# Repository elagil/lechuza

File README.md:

# Lechuza (owl)

A columnar-stagger single-piece keyboard.

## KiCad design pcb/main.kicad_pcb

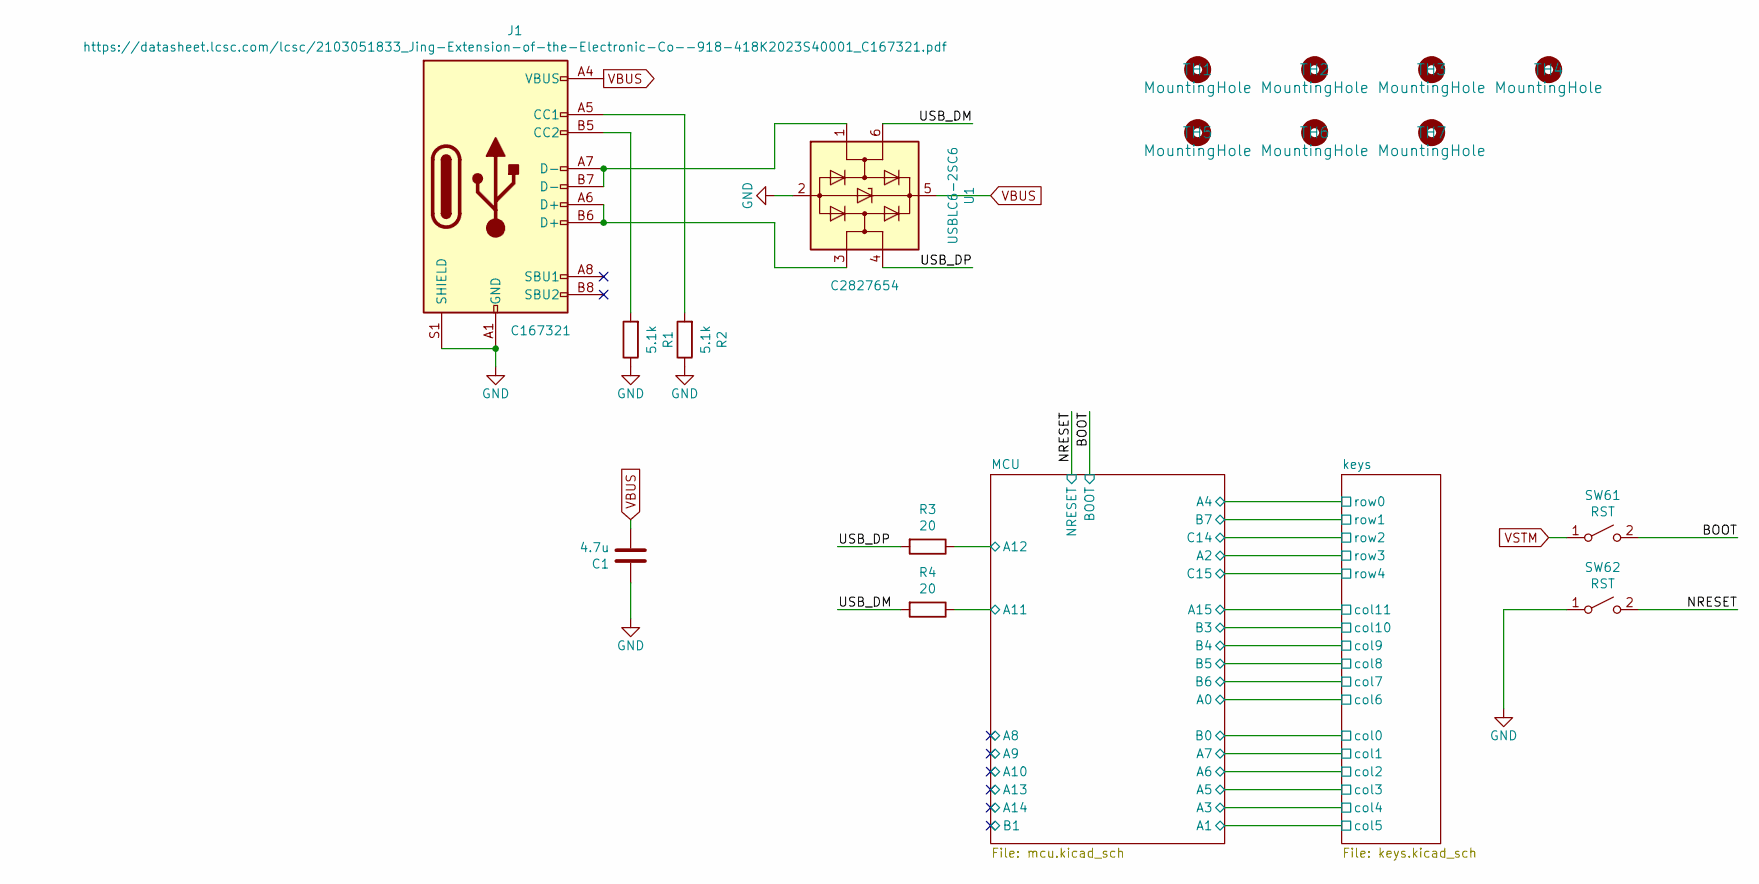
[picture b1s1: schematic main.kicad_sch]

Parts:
C1: 4.7u; C_0603_1608Metric; LCSC C19666
J1: https://datasheet.lcsc.com/lcsc/2103051833_Jing-E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; USB_C_Receptacle_XKB_U262-16XN-4BVC11; LCSC C167321
R1, R2: 5.1k; R_0603_1608Metric; LCSC C23186
R3, R4: 20; R_0603_1608Metric; LCSC C22950
SW61, SW62: RST; SW_SPST_TL3342; LCSC C318884
TH1, TH2, TH3, TH4, TH5, TH6, TH7: MountingHole; Mounting_Wuerth_WA-SMSR-3.2mm_H5.1mm_ReverseMount_9775051960
U1: USBLC6-2SC6; SOT-23-6; LCSC C2827654

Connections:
/BOOT: SW61.2 (B); also elsewhere on the board
/MCU/A11: R4.1; also elsewhere on the board
/MCU/A12: R3.1; also elsewhere on the board
/NRESET: SW62.2 (B); also elsewhere on the board
/USB_DM: R4.2, U1.6 (I/O1)
/USB_DP: R3.2, U1.4 (I/O2)
GND: C1.1, J1.A1 (GND), J1.A12 (GND), J1.B1 (GND), J1.B12 (GND), J1.S1 (SHIELD), R1.1, R2.1, SW62.1 (A), U1.2 (GND); also elsewhere on the board
unnamed: J1.A5 (CC1), R2.2
unnamed: J1.A6 (D+), J1.B6 (D+), U1.3 (I/O2)
unnamed: J1.A7 (D-), J1.B7 (D-), U1.1 (I/O1)
unnamed: J1.B5 (CC2), R1.2
VBUS: C1.2, J1.A4 (VBUS), J1.A9 (VBUS), J1.B4 (VBUS), J1.B9 (VBUS), U1.5 (VBUS); also elsewhere on the board
VSTM: SW61.1 (A); also elsewhere on the board

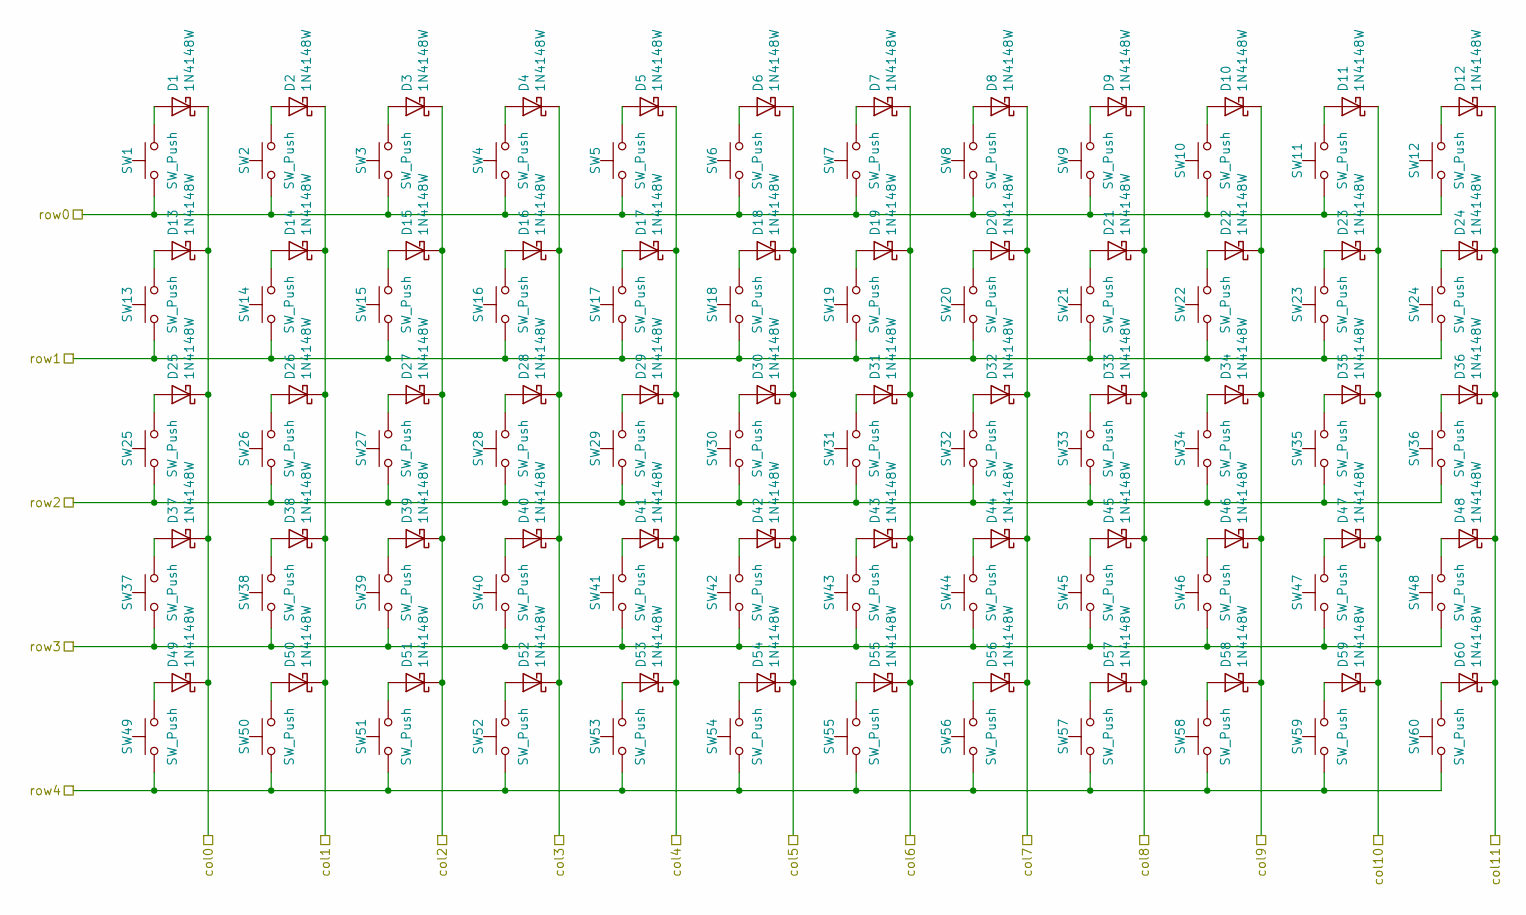
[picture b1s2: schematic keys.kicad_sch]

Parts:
D1, D2, D3, D4, D5, D6, D7, D8, D9, D10, D11, D12, D13, D14, D15, D16, D17, D18, D19, D20, D21, D22, D23, D24, D25, D26, D27, D28, D29, D30, D31, D32, D33, D34, D35, D36, D37, D38, D39, D40, D41, D42, D43, D44, D45, D46, D47, D48, D49, D50, D51, D52, D53, D54, D55, D56, D57, D58, D59, D60: 1N4148W; D_SOD-123; LCSC C81598
SW1, SW2, SW3, SW4, SW5, SW6, SW7, SW8, SW9, SW10, SW11, SW12, SW13, SW14, SW15, SW16, SW17, SW18, SW19, SW20, SW21, SW22, SW23, SW24, SW25, SW26, SW27, SW28, SW29, SW30, SW31, SW32, SW33, SW34, SW35, SW36, SW37, SW38, SW39, SW40, SW41, SW42, SW43, SW44, SW45, SW46, SW47, SW48, SW49, SW50, SW51, SW53, SW54, SW55, SW56, SW58, SW59, SW60: SW_Push; SW_Cherry_MX_1.00u_PCB
SW52, SW57: SW_Push; SW_Cherry_MX_1.50u_PCB

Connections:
/MCU/A0: D7.1 (K), D19.1 (K), D31.1 (K), D43.1 (K), D55.1 (K); also elsewhere on the board
/MCU/A1: D6.1 (K), D18.1 (K), D30.1 (K), D42.1 (K), D54.1 (K); also elsewhere on the board
/MCU/A2: SW37.1, SW38.1, SW39.1, SW40.1, SW41.1, SW42.1, SW43.1, SW44.1, SW45.1, SW46.1, SW47.1, SW48.1; also elsewhere on the board
/MCU/A3: D5.1 (K), D17.1 (K), D29.1 (K), D41.1 (K), D53.1 (K); also elsewhere on the board
/MCU/A4: SW1.1, SW2.1, SW3.1, SW4.1, SW5.1, SW6.1, SW7.1, SW8.1, SW9.1, SW10.1, SW11.1, SW12.1; also elsewhere on the board
/MCU/A5: D4.1 (K), D16.1 (K), D28.1 (K), D40.1 (K), D52.1 (K); also elsewhere on the board
/MCU/A6: D3.1 (K), D15.1 (K), D27.1 (K), D39.1 (K), D51.1 (K); also elsewhere on the board
/MCU/A7: D2.1 (K), D14.1 (K), D26.1 (K), D38.1 (K), D50.1 (K); also elsewhere on the board
/MCU/A15: D12.1 (K), D24.1 (K), D36.1 (K), D48.1 (K), D60.1 (K); also elsewhere on the board
/MCU/B0: D1.1 (K), D13.1 (K), D25.1 (K), D37.1 (K), D49.1 (K); also elsewhere on the board
/MCU/B3: D11.1 (K), D23.1 (K), D35.1 (K), D47.1 (K), D59.1 (K); also elsewhere on the board
/MCU/B4: D10.1 (K), D22.1 (K), D34.1 (K), D46.1 (K), D58.1 (K); also elsewhere on the board
/MCU/B5: D9.1 (K), D21.1 (K), D33.1 (K), D45.1 (K), D57.1 (K); also elsewhere on the board
/MCU/B6: D8.1 (K), D20.1 (K), D32.1 (K), D44.1 (K), D56.1 (K); also elsewhere on the board
/MCU/B7: SW13.1, SW14.1, SW15.1, SW16.1, SW17.1, SW18.1, SW19.1, SW20.1, SW21.1, SW22.1, SW23.1, SW24.1; also elsewhere on the board
/MCU/C14: SW25.1, SW26.1, SW27.1, SW28.1, SW29.1, SW30.1, SW31.1, SW32.1, SW33.1, SW34.1, SW35.1, SW36.1; also elsewhere on the board
/MCU/C15: SW49.1, SW50.1, SW51.1, SW52.1, SW53.1, SW54.1, SW55.1, SW56.1, SW57.1, SW58.1, SW59.1, SW60.1; also elsewhere on the board
unnamed: D1.2 (A), SW1.2
unnamed: D2.2 (A), SW2.2
unnamed: D3.2 (A), SW3.2
unnamed: D4.2 (A), SW4.2
unnamed: D5.2 (A), SW5.2
unnamed: D6.2 (A), SW6.2
unnamed: D7.2 (A), SW7.2
unnamed: D8.2 (A), SW8.2
unnamed: D9.2 (A), SW9.2
unnamed: D10.2 (A), SW10.2
unnamed: D11.2 (A), SW11.2
unnamed: D12.2 (A), SW12.2
unnamed: D13.2 (A), SW13.2
unnamed: D14.2 (A), SW14.2
unnamed: D15.2 (A), SW15.2
unnamed: D16.2 (A), SW16.2
unnamed: D17.2 (A), SW17.2
unnamed: D18.2 (A), SW18.2
unnamed: D19.2 (A), SW19.2
unnamed: D20.2 (A), SW20.2
unnamed: D21.2 (A), SW21.2
unnamed: D22.2 (A), SW22.2
unnamed: D23.2 (A), SW23.2
unnamed: D24.2 (A), SW24.2
unnamed: D25.2 (A), SW25.2
unnamed: D26.2 (A), SW26.2
unnamed: D27.2 (A), SW27.2
unnamed: D28.2 (A), SW28.2
unnamed: D29.2 (A), SW29.2
unnamed: D30.2 (A), SW30.2
unnamed: D31.2 (A), SW31.2
unnamed: D32.2 (A), SW32.2
unnamed: D33.2 (A), SW33.2
unnamed: D34.2 (A), SW34.2
unnamed: D35.2 (A), SW35.2
unnamed: D36.2 (A), SW36.2
unnamed: D37.2 (A), SW37.2
unnamed: D38.2 (A), SW38.2
unnamed: D39.2 (A), SW39.2
unnamed: D40.2 (A), SW40.2
unnamed: D41.2 (A), SW41.2
unnamed: D42.2 (A), SW42.2
unnamed: D43.2 (A), SW43.2
unnamed: D44.2 (A), SW44.2
unnamed: D45.2 (A), SW45.2
unnamed: D46.2 (A), SW46.2
unnamed: D47.2 (A), SW47.2
unnamed: D48.2 (A), SW48.2
unnamed: D49.2 (A), SW49.2
unnamed: D50.2 (A), SW50.2
unnamed: D51.2 (A), SW51.2
unnamed: D52.2 (A), SW52.2
unnamed: D53.2 (A), SW53.2
unnamed: D54.2 (A), SW54.2
unnamed: D55.2 (A), SW55.2
unnamed: D56.2 (A), SW56.2
unnamed: D57.2 (A), SW57.2
unnamed: D58.2 (A), SW58.2
unnamed: D59.2 (A), SW59.2
unnamed: D60.2 (A), SW60.2

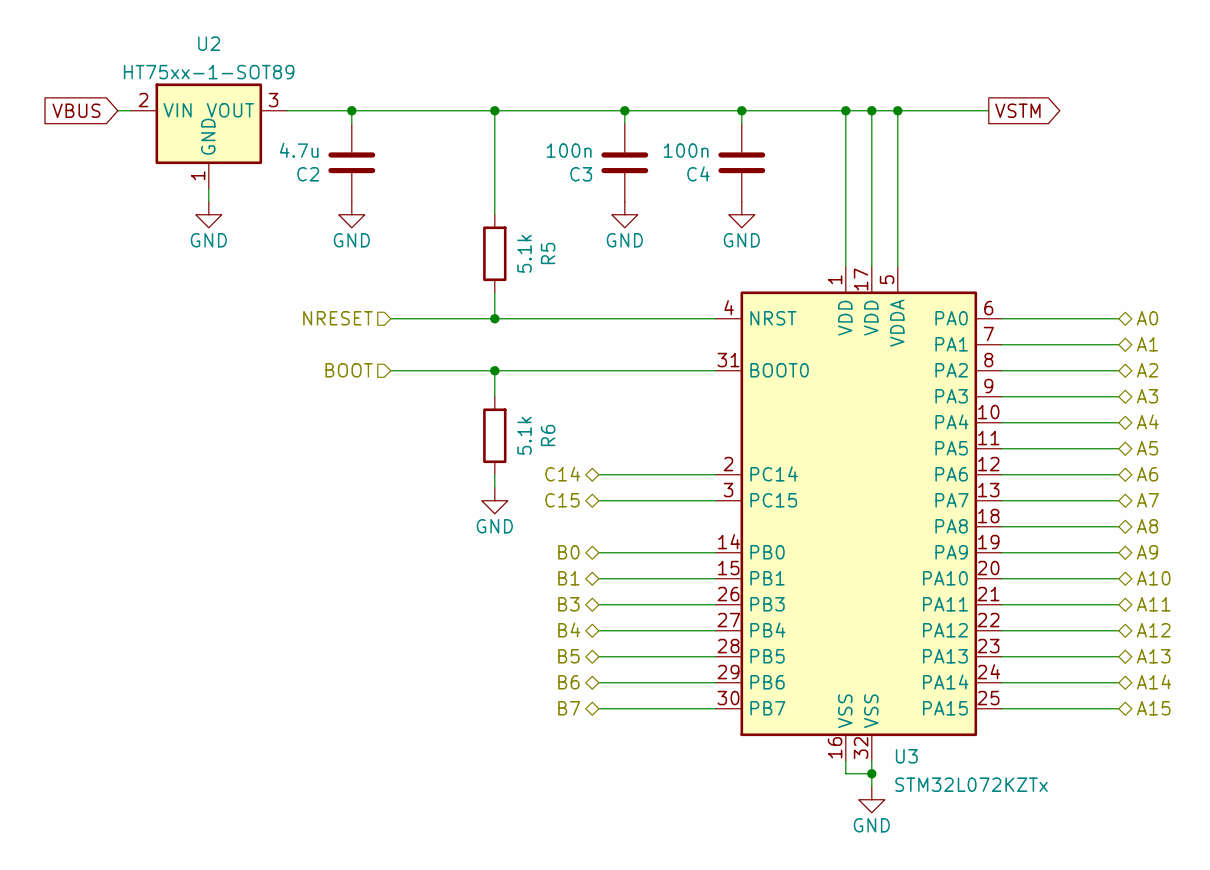
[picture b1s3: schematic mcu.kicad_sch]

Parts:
C2: 4.7u; C_0603_1608Metric; LCSC C19666
C3, C4: 100n; C_0603_1608Metric; LCSC C14663
R5, R6: 5.1k; R_0603_1608Metric; LCSC C23186
U2: HT75xx-1-SOT89; SOT-89-3; LCSC C14289
U3: STM32L072KZTx; LQFP-32_7x7mm_P0.8mm

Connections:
/BOOT: R6.2, U3.31 (BOOT0); also elsewhere on the board
/MCU/A0: U3.6 (PA0); also elsewhere on the board
/MCU/A1: U3.7 (PA1); also elsewhere on the board
/MCU/A2: U3.8 (PA2); also elsewhere on the board
/MCU/A3: U3.9 (PA3); also elsewhere on the board
/MCU/A4: U3.10 (PA4); also elsewhere on the board
/MCU/A5: U3.11 (PA5); also elsewhere on the board
/MCU/A6: U3.12 (PA6); also elsewhere on the board
/MCU/A7: U3.13 (PA7); also elsewhere on the board
/MCU/A8: U3.18 (PA8)
/MCU/A9: U3.19 (PA9)
/MCU/A10: U3.20 (PA10)
/MCU/A11: U3.21 (PA11); also elsewhere on the board
/MCU/A12: U3.22 (PA12); also elsewhere on the board
/MCU/A13: U3.23 (PA13)
/MCU/A14: U3.24 (PA14)
/MCU/A15: U3.25 (PA15); also elsewhere on the board
/MCU/B0: U3.14 (PB0); also elsewhere on the board
/MCU/B1: U3.15 (PB1)
/MCU/B3: U3.26 (PB3); also elsewhere on the board
/MCU/B4: U3.27 (PB4); also elsewhere on the board
/MCU/B5: U3.28 (PB5); also elsewhere on the board
/MCU/B6: U3.29 (PB6); also elsewhere on the board
/MCU/B7: U3.30 (PB7); also elsewhere on the board
/MCU/C14: U3.2 (PC14); also elsewhere on the board
/MCU/C15: U3.3 (PC15); also elsewhere on the board
/NRESET: R5.1, U3.4 (NRST); also elsewhere on the board
GND: C2.1, C3.1, C4.1, R6.1, U2.1 (GND), U3.16 (VSS), U3.32 (VSS); also elsewhere on the board
VBUS: U2.2 (VIN); also elsewhere on the board
VSTM: C2.2, C3.2, C4.2, R5.2, U2.3 (VOUT), U3.1 (VDD), U3.5 (VDDA), U3.17 (VDD); also elsewhere on the board

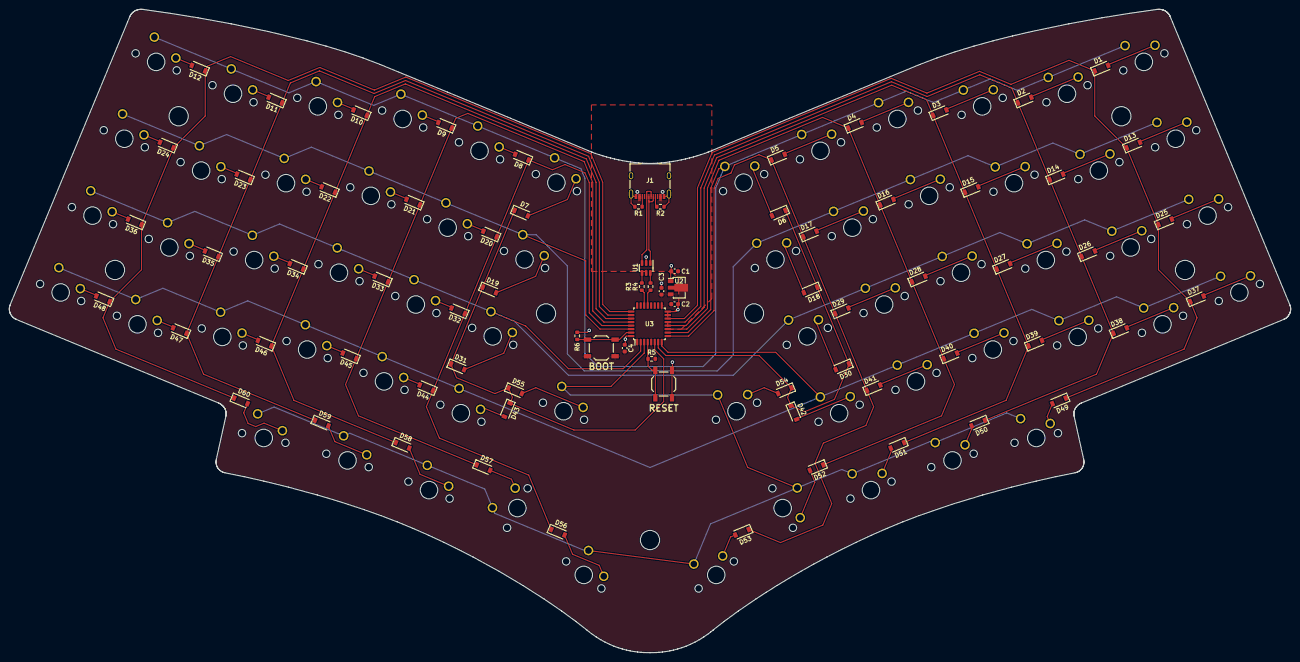
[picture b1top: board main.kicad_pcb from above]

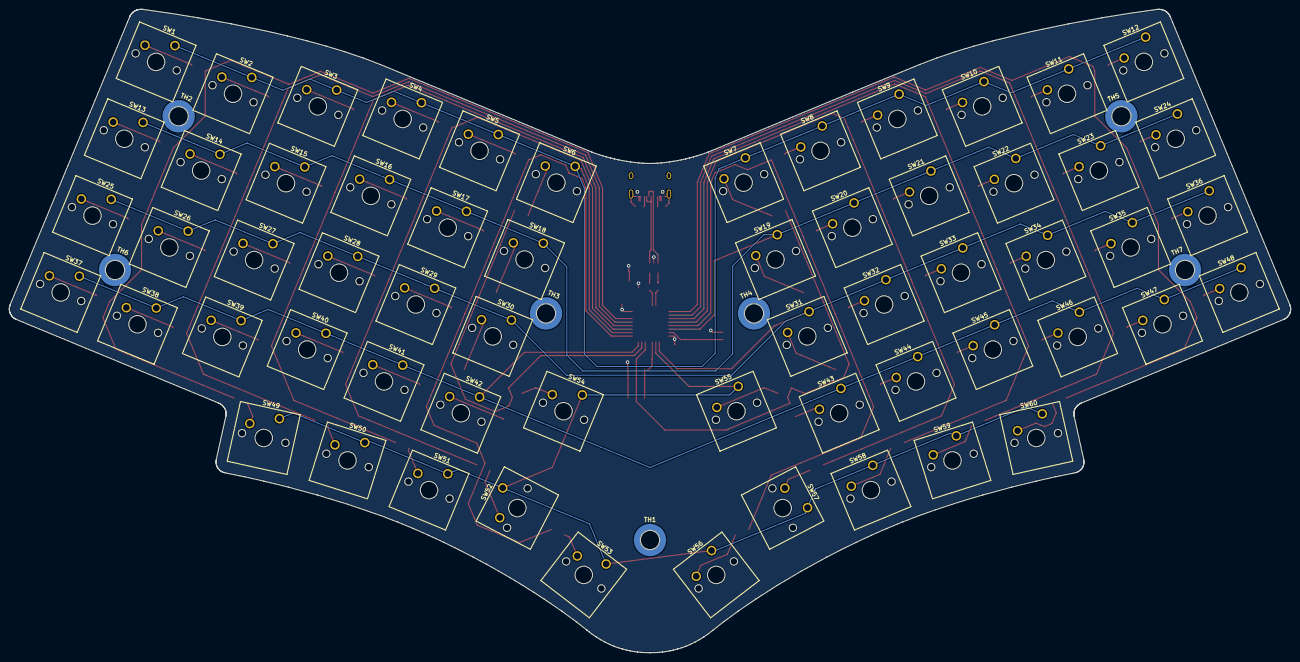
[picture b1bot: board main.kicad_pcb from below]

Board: 2 copper layers, 292.6 x 146.9 mm, 143 parts (67 on the bottom side), 90 nets.

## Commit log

2022-02-20 Added .gitignore
2022-02-26 finalized design
2022-02-26 Gerber for production run
2022-03-22 Fixed missing columns, fixed USB-C connector position, new LDO
